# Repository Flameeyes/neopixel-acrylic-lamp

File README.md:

<!--
SPDX-FileCopyrightText: 2020 Diego Elio Pettenò

SPDX-License-Identifier: MIT
-->

# Neopixel Acrylic Lamp

This repository contains Eagle PCB dsigns and 3D objects to build a lamp hosting an acrylic
cutout, similar to the many "3D effect" lamps that you can buy on most online stores by now.

Please note that while rev3 boards appear to be working, the 3D objects are still untested
and the design is still up in the air.

## Further References

Refer to my [blog](https://flameeyes.blog/tag/acrylic-lamps/) for
details.

## License

Copyright 2020 Diego Elio Pettenò

Permission is hereby granted, free of charge, to any person obtaining a copy of this
software and associated documentation files (the "Software"), to deal in the Software
without restriction, including without limitation the rights to use, copy, modify,
merge, publish, distribute, sublicense, and/or sell copies of the Software, and to
permit persons to whom the Software is furnished to do so, subject to the following
conditions:

The above copyright notice and this permission notice shall be included in all copies or
substantial portions of the Software.

THE SOFTWARE IS PROVIDED "AS IS", WITHOUT WARRANTY OF ANY KIND, EXPRESS OR IMPLIED,
INCLUDING BUT NOT LIMITED TO THE WARRANTIES OF MERCHANTABILITY, FITNESS FOR A PARTICULAR
PURPOSE AND NONINFRINGEMENT. IN NO EVENT SHALL THE AUTHORS OR COPYRIGHT HOLDERS BE
LIABLE FOR ANY CLAIM, DAMAGES OR OTHER LIABILITY, WHETHER IN AN ACTION OF CONTRACT, TORT
OR OTHERWISE, ARISING FROM, OUT OF OR IN CONNECTION WITH THE SOFTWARE OR THE USE OR
OTHER DEALINGS IN THE SOFTWARE.

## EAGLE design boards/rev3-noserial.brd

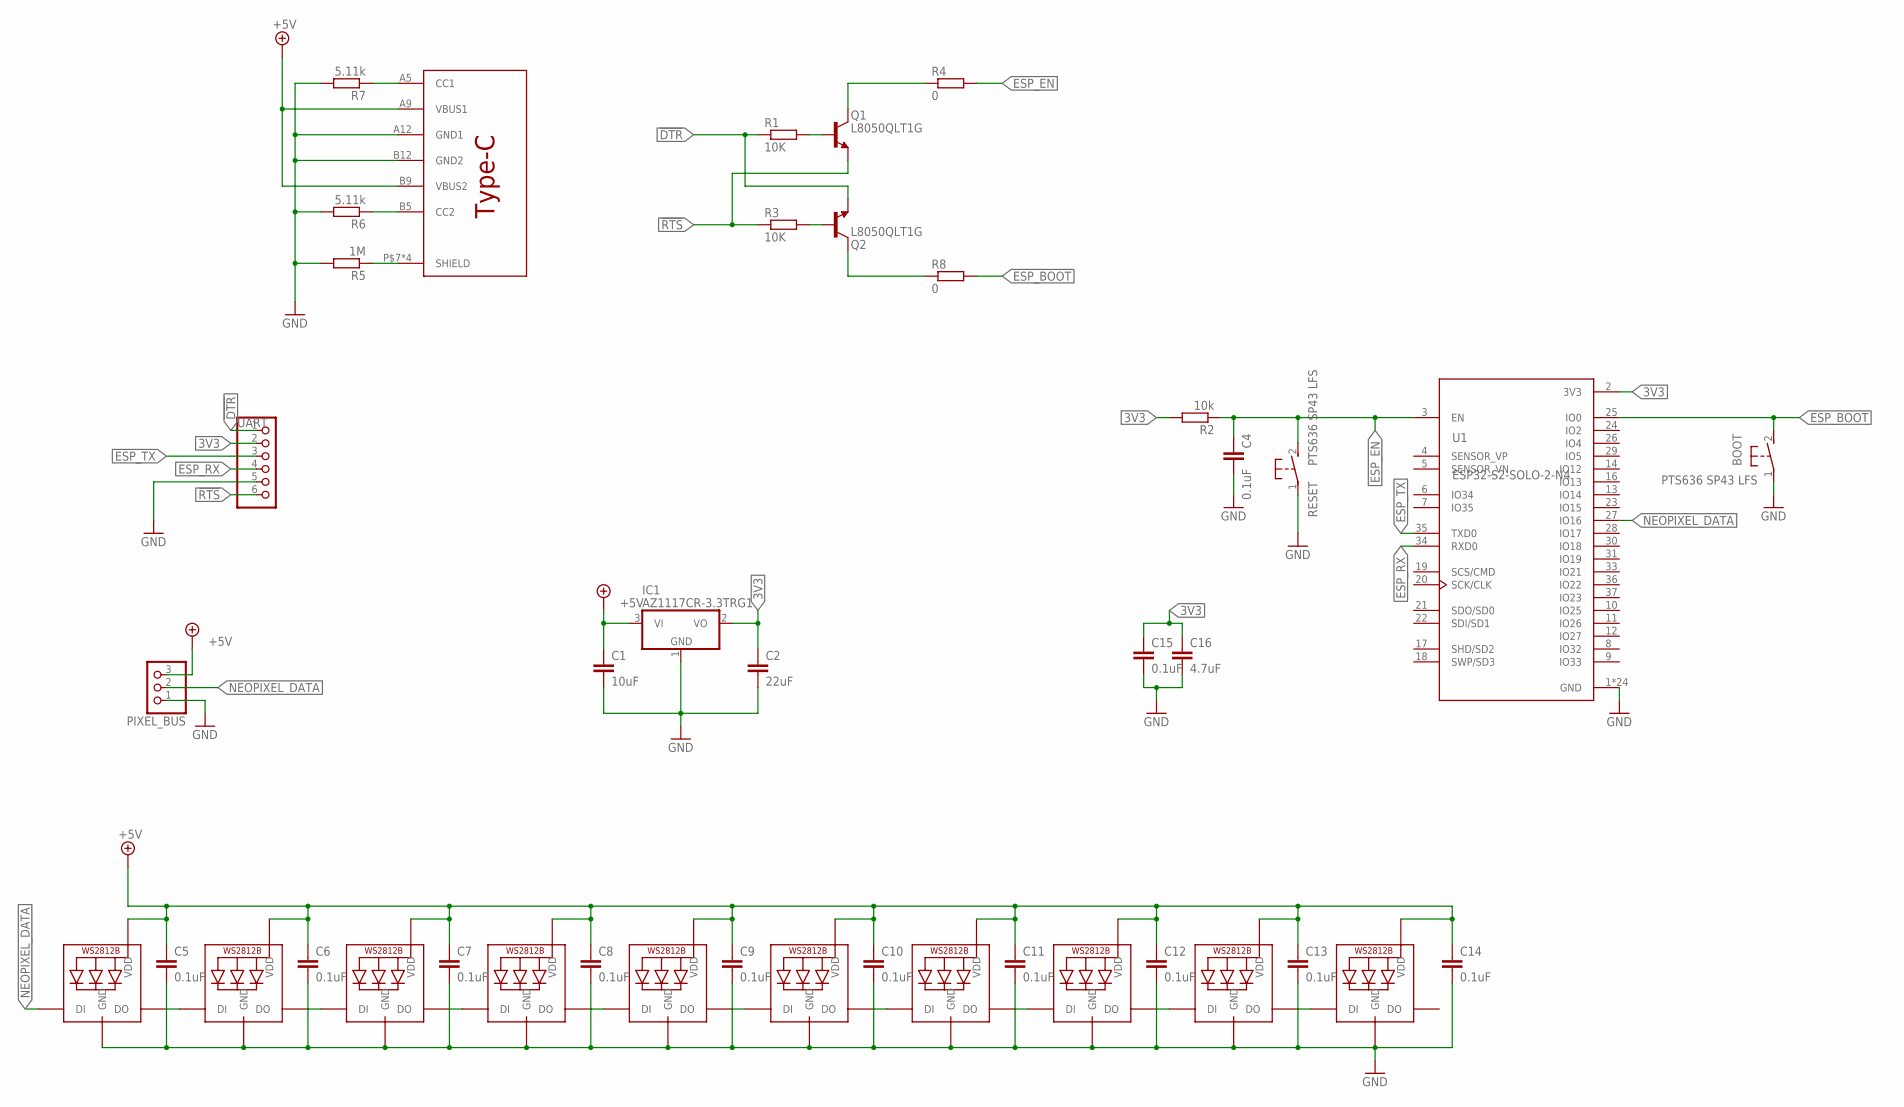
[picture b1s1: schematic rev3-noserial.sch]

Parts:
BOOT: PTS636 SP43 LFS; PTS636SP43LFS
C1: 10uF; C0805
C2: 22uF; C0805
C4, C5, C6, C7, C8, C9, C10, C11, C12, C13, C14, C15: 0.1uF; C0805
C16: 4.7uF; C0805
IC1: AZ1117CR-3.3TRG1; SOT89
LED1, LED2, LED3, LED4, LED5, LED6, LED7, LED8, LED9, LED10: WS2812B5050; WS2812B
PIXEL_BUS: PINHD-1X3; 1X03
Q1, Q2: L8050QLT1G; SOT95P237X112-3N
R1, R3: 10K; R0805
R2: 10k; R0805
R4, R8: 0; R0805
R5: 1M; R0805
R6, R7: 5.11k; R0805
RESET: PTS636 SP43 LFS; PTS636SP43LFS
U1: ESP32-S2-SOLO-2-N4; MODULE_ESP32-WROOM-32D
U$1: TYPEC-DB-104PWB
UART: PINHD-1X6; 1X06

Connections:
3V3: C2.1, C15.1, C16.1, IC1.2 (VO), R2.2, U1.2 (3V3), UART.2
!DTR: Q2.2 (E), R1.1, UART.1
!RTS: Q1.2 (E), R3.1, UART.6
+5V: C1.1, C5.1, C6.1, C7.1, C8.1, C9.1, C10.1, C11.1, C12.1, C13.1, C14.1, IC1.3 (VI), LED1.1-VDD (VDD), LED2.1-VDD (VDD), LED3.1-VDD (VDD), LED4.1-VDD (VDD), LED5.1-VDD (VDD), LED6.1-VDD (VDD), LED7.1-VDD (VDD), LED8.1-VDD (VDD), LED9.1-VDD (VDD), LED10.1-VDD (VDD), PIXEL_BUS.3, U$1.A9 (VBUS1), U$1.B9 (VBUS2)
ESP_BOOT: BOOT.2, R8.2, U1.25 (IO0)
ESP_EN: C4.1, R2.1, R4.2, RESET.2, U1.3 (EN)
ESP_RX: U1.34 (RXD0), UART.4
ESP_TX: U1.35 (TXD0), UART.3
GND: BOOT.1, C1.2, C2.2, C4.2, C5.2, C6.2, C7.2, C8.2, C9.2, C10.2, C11.2, C12.2, C13.2, C14.2, C15.2, C16.2, IC1.1 (GND), LED1.3-GND (GND), LED2.3-GND (GND), LED3.3-GND (GND), LED4.3-GND (GND), LED5.3-GND (GND), LED6.3-GND (GND), LED7.3-GND (GND), LED8.3-GND (GND), LED9.3-GND (GND), LED10.3-GND (GND), PIXEL_BUS.1, R5.2, R6.2, R7.2, RESET.1, U1.1 (GND), U1.15 (GND), U1.38 (GND), U1.39_1 (GND), U1.39_2 (GND), U1.39_3 (GND), U1.39_4 (GND), U1.39_5 (GND), U1.39_6 (GND), U1.39_7 (GND), U1.39_8 (GND), U1.39_9 (GND), U1.39_10 (GND), U1.39_11 (GND), U1.39_12 (GND), U1.39_13 (GND), U1.39_14 (GND), U1.39_15 (GND), U1.39_16 (GND), U1.39_17 (GND), U1.39_18 (GND), U1.39_19 (GND), U1.39_20 (GND), U1.39_21 (GND), U$1.A12 (GND1), U$1.B12 (GND2), UART.5
unnamed: R6.1, U$1.B5 (CC2)
unnamed: R5.1, U$1.P$7 (SHIELD), U$1.P$8 (SHIELD), U$1.P$9 (SHIELD), U$1.P$10 (SHIELD)
unnamed: R7.1, U$1.A5 (CC1)
unnamed: LED2.2-DOUT (DO), LED3.4-DIN (DI)
unnamed: Q1.1 (B), R1.2
unnamed: Q2.1 (B), R3.2
unnamed: LED3.2-DOUT (DO), LED4.4-DIN (DI)
unnamed: Q1.3 (C), R4.1
unnamed: Q2.3 (C), R8.1
unnamed: LED4.2-DOUT (DO), LED5.4-DIN (DI)
unnamed: LED5.2-DOUT (DO), LED6.4-DIN (DI)
unnamed: LED6.2-DOUT (DO), LED7.4-DIN (DI)
unnamed: LED7.2-DOUT (DO), LED8.4-DIN (DI)
unnamed: LED8.2-DOUT (DO), LED9.4-DIN (DI)
unnamed: LED9.2-DOUT (DO), LED10.4-DIN (DI)
unnamed: LED1.2-DOUT (DO), LED2.4-DIN (DI)
NEOPIXEL_DATA: LED1.4-DIN (DI), PIXEL_BUS.2, U1.27 (IO16)

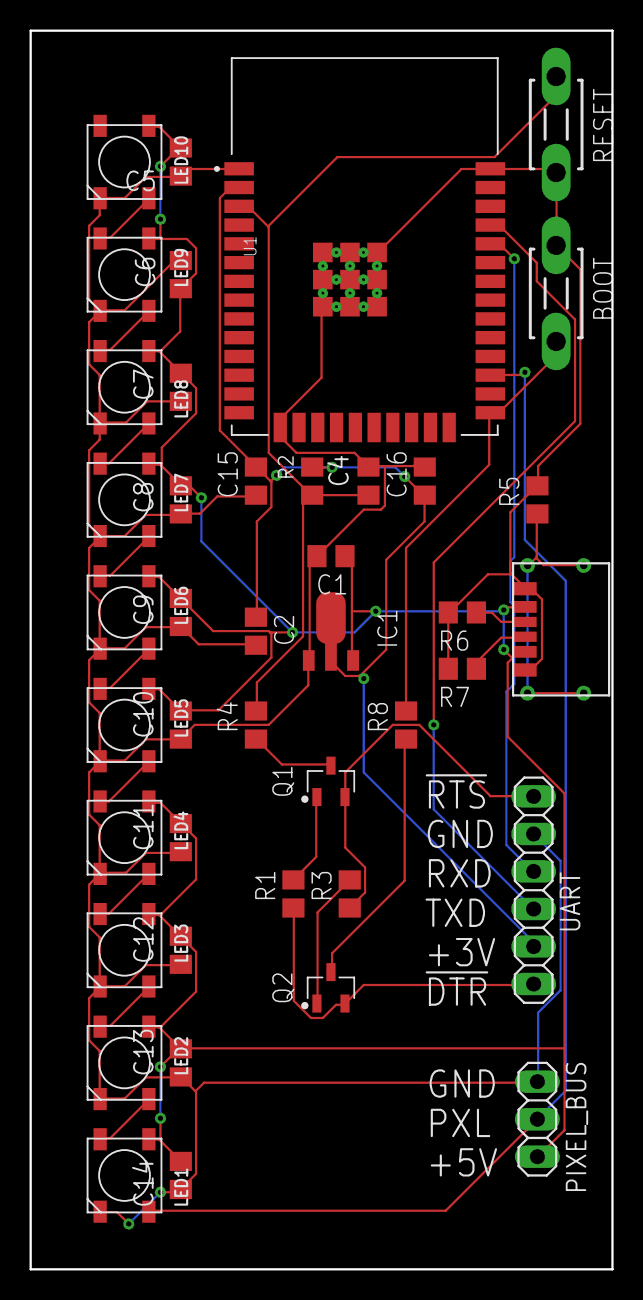
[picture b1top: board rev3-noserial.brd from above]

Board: 2 copper layers, 39.4 x 83.8 mm, 42 parts (0 on the bottom side), 26 nets.

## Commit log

2020-07-18 Tag trivial files with 0BSD license.
    This allows SPDX compliance.
2020-07-18 Add a basic README file.
2020-07-18 Add the d-board schematics.
2020-07-20 Update board to rev.2
    Fixes CP2104 REGIN not connected to +5V.
    Replaces the mis-pinned 3535 neopixel with the 5050 part that is correct instead.
2020-07-24 Replace the microUSB connector.
    Instead of the Wurth part that seems to be harder to find, use a SnapEDA for an Amphenol 10103594-0001LF connector that appears easier to source.
2020-08-31 Make it possible to program the ESP32 via serial.
    This includes RESET and BOOT pushbuttons to control a solder ESP32, and re-wires the RTS/DTR to control the boot mode of the board for compatibility with the esptool command line.
2020-09-02 Replace the CP2104 with a CP2102
    The CP2104 is getting harder to source, the CP2102 is pretty much equivalent, but requires more components.
2020-09-12 Use net names instead of very long connections.
    This allows an easier read of the diagram.
2020-09-12 Add a warning that the project is not working.
    I haven't managed to get this to work with four attempts. I'm unlikely to go through with it.
2023-07-02 Introduce rev3 and remove non-functional d-board.
    The d-shaped board never worked, remove it.
    The new rev3 is not meant to replace the existing boards in the AliExpress bases but rather includes its own 3D-printed base.
2023-07-09 Update the no-serial design for autoprogram.
    This includes the same design block as the ESP32 WROOM-like modules, which means it should be possible to auto-program the boards without needing to solder in buttons.
2023-07-15 Update base.
    This raises the feet to make sure the screw hides properly behind it, and tries to improve on the slot in mechanism for the door.
2023-10-29 Point at the blog's tag instead of a single post.
    I have written more on this, and it's now working, so point at something that is more informative.

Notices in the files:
boards/rev3-noserial.brd:
Neopixel Acrylic Lamp rev. 3.1 - Licensed under MIT
Copyright © 2023 Diego Elio Pettenò - defp.uk/espacrylic
